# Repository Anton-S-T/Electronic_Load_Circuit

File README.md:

#Electronic_Load_Circuit

A circuit to sink 3A at a Voltage of up to 30V

Layout:

WIP

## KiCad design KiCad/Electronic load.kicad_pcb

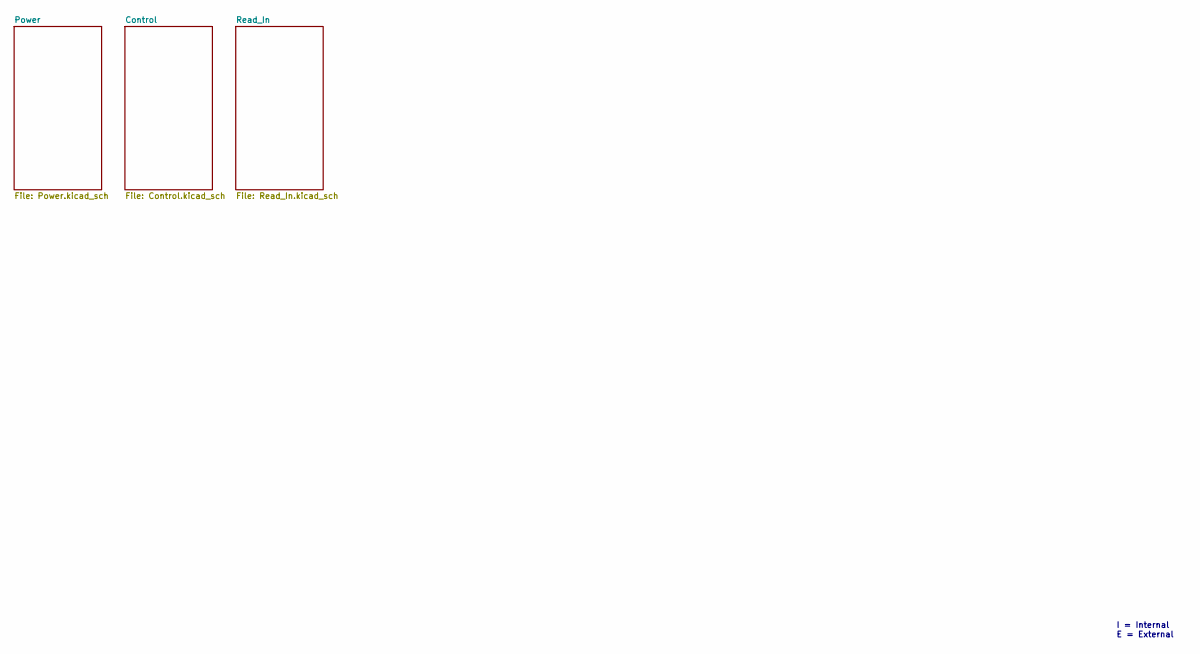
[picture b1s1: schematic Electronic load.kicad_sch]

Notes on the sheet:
I = Internal E = External

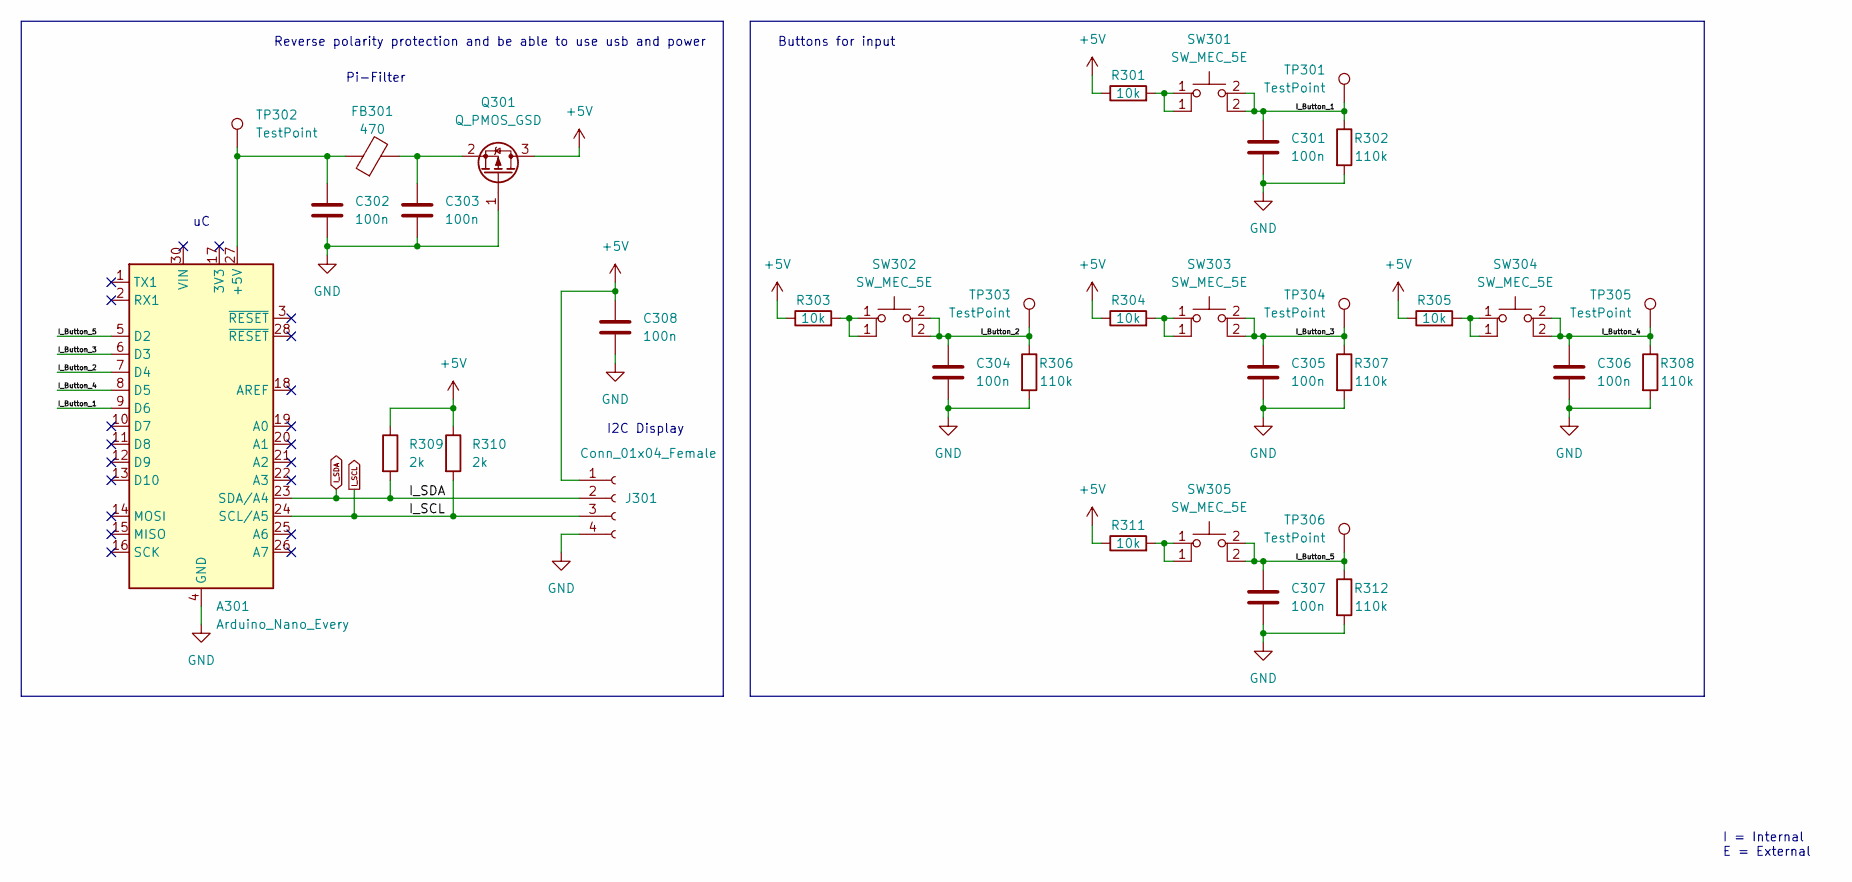
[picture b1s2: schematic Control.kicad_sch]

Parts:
A301: Arduino_Nano_Every; Arduino_Nano
C301, C302, C303, C304, C305, C306, C307, C308: 100n; C_0603_1608Metric
FB301: 470; R_0603_1608Metric
J301: Conn_01x04_Female; TerminalBlock_bornier-4_P5.08mm
Q301: Q_PMOS_GSD; SOT-23
R301, R303, R304, R305, R311: 10k; R_0603_1608Metric
R302, R306, R307, R308, R312: 110k; R_0603_1608Metric
R309, R310: 2k; R_0805_2012Metric
SW301, SW302, SW303, SW304, SW305: SW_MEC_5E; SW_PUSH_6mm
TP301, TP302, TP303, TP304, TP305, TP306: TestPoint; TestPoint_Pad_D1.0mm

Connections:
+5V: C308.1, J301.1, Q301.3 (D), R301.1, R303.1, R304.1, R305.1, R309.1, R310.1, R311.1; also elsewhere on the board
/Control/I_Button_1: A301.9 (D6), C301.1, R302.1, SW301.2 (K), TP301.1
/Control/I_Button_2: A301.7 (D4), C304.1, R306.1, SW302.2 (K), TP303.1
/Control/I_Button_3: A301.6 (D3), C305.1, R307.1, SW303.2 (K), TP304.1
/Control/I_Button_4: A301.8 (D5), C306.1, R308.1, SW304.2 (K), TP305.1
/Control/I_Button_5: A301.5 (D2), C307.1, R312.1, SW305.2 (K), TP306.1
GND: A301.4 (GND), A301.29 (GND), C301.2, C302.2, C303.2, C304.2, C305.2, C306.2, C307.2, C308.2, J301.4, Q301.1 (G), R302.2, R306.2, R307.2, R308.2, R312.2; also elsewhere on the board
I_SCL: A301.24 (SCL/A5), J301.3, R310.2; also elsewhere on the board
I_SDA: A301.23 (SDA/A4), J301.2, R309.2; also elsewhere on the board
unnamed: A301.27 (+5V), C302.1, FB301.1, TP302.1
unnamed: C303.1, FB301.2, Q301.2 (S)
unnamed: R301.2, SW301.1
unnamed: R303.2, SW302.1
unnamed: R304.2, SW303.1
unnamed: R305.2, SW304.1
unnamed: R311.2, SW305.1

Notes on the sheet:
Pi-Filter
I = Internal E = External
Buttons for input
I2C Display
Reverse polarity protection and be able to use usb and power

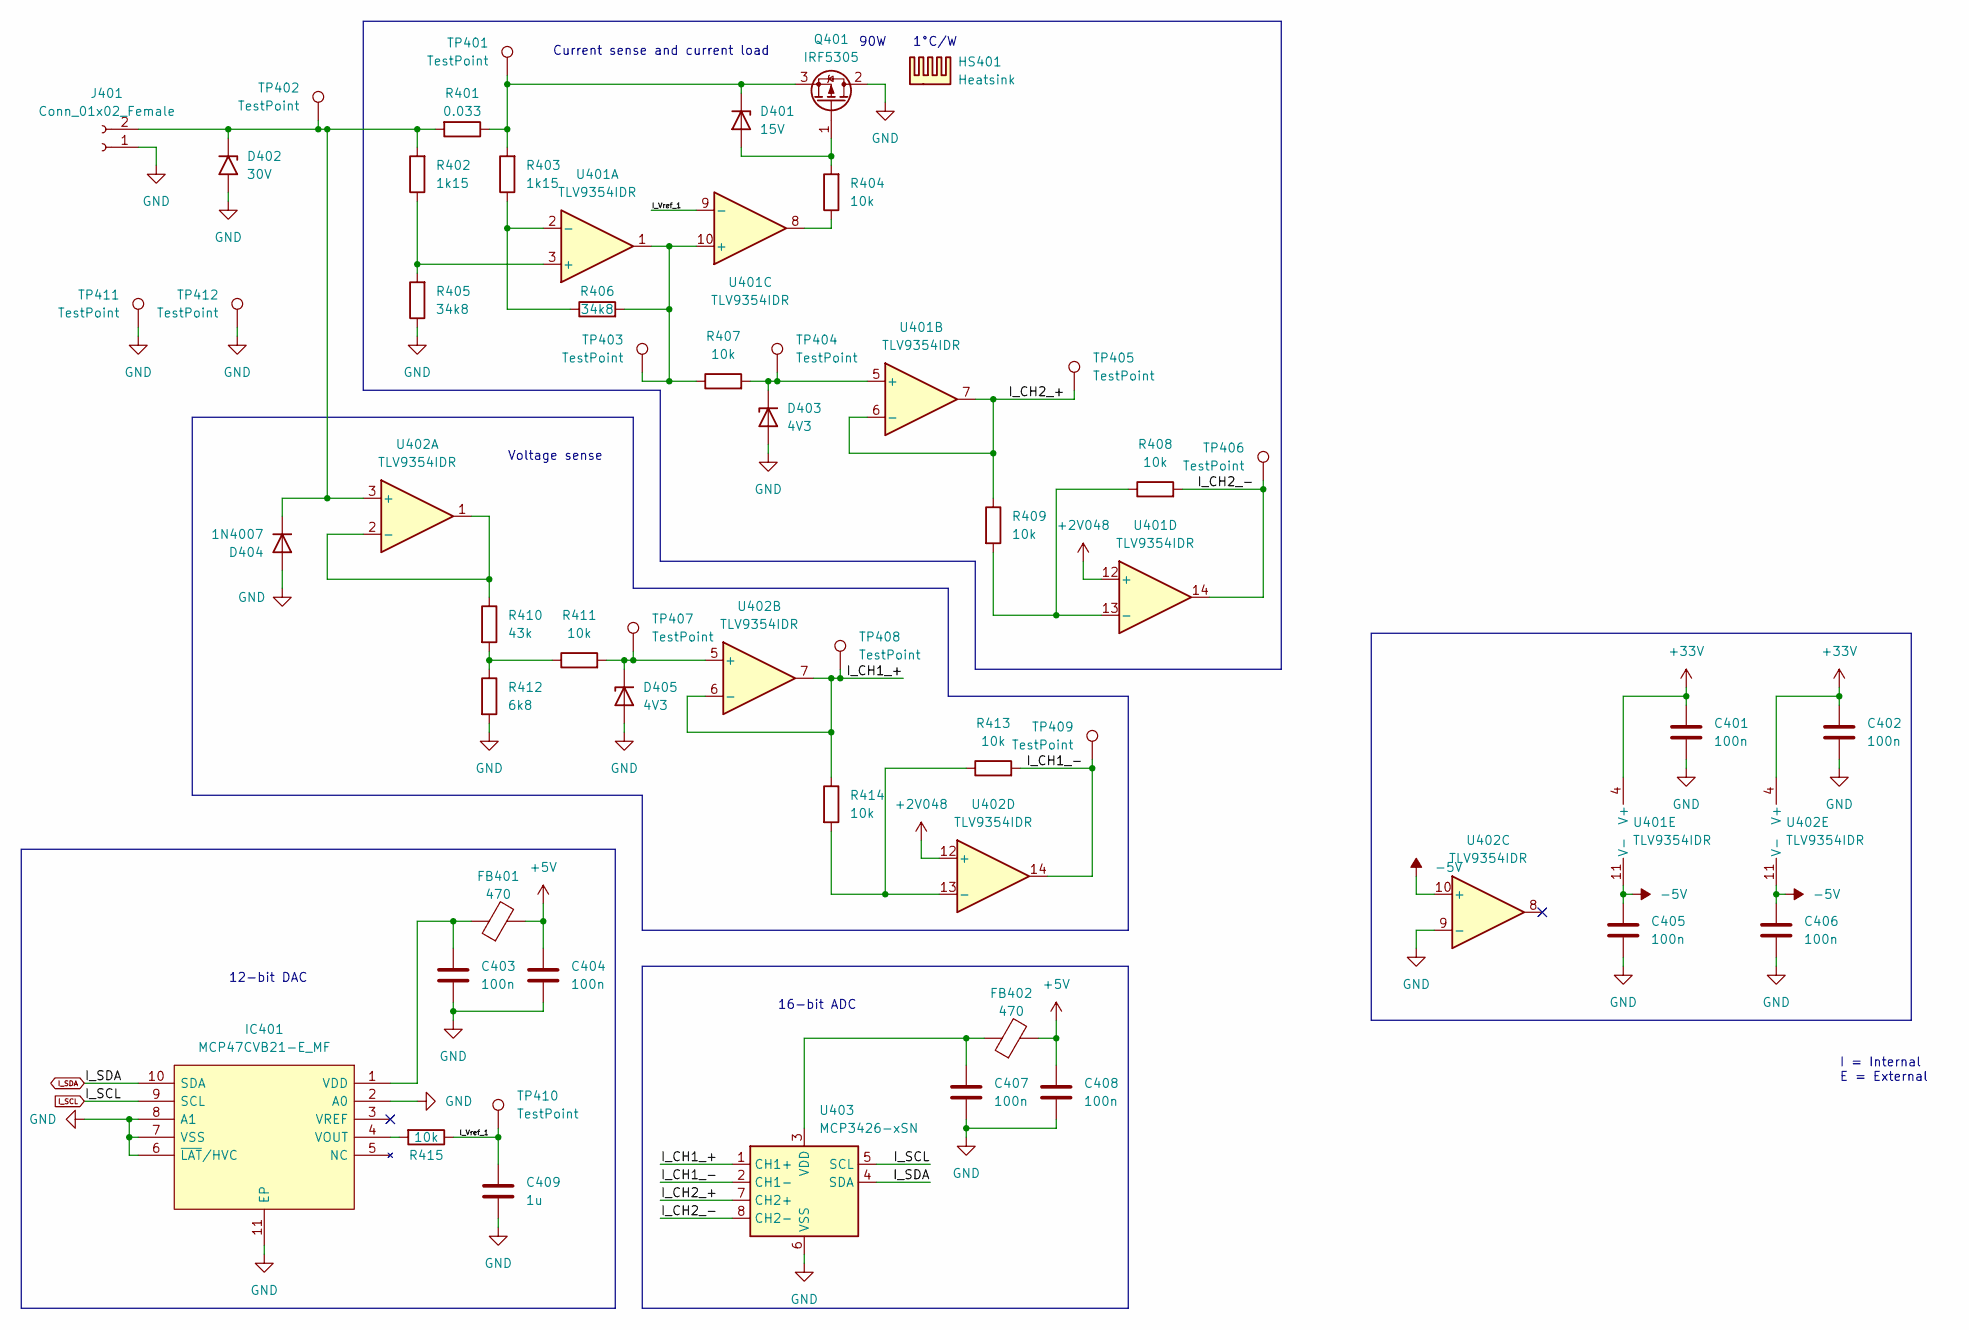
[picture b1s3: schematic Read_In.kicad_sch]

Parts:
C401, C402, C403, C404, C405, C406, C407, C408: 100n; C_0603_1608Metric
C409: 1u; C_0603_1608Metric
D401: 15V; D_SOD-123
D402: 30V; D_SMB
D403, D405: 4V3; D_SOD-123
D404: 1N4007; D_DO-41_SOD81_P10.16mm_Horizontal
FB401, FB402: 470; R_0603_1608Metric
HS401: Heatsink
IC401: MCP47CVB21-E_MF; DFN-10-1EP_3x3mm_P0.5mm_EP1.65x2.38mm_ThermalVias; Mouser Part Number 579-MCP47CVB21-E/MF
J401: Conn_01x02_Female; TerminalBlock_bornier-2_P5.08mm
Q401: IRF5305; TO-220-3_Vertical
R401: 0.033; R_1206_3216Metric
R402, R403: 1k15; R_0805_2012Metric
R404, R407, R408, R409, R411, R413, R414, R415: 10k; R_0603_1608Metric
R405, R406: 34k8; R_0603_1608Metric
R410: 43k; R_0603_1608Metric
R412: 6k8; R_0603_1608Metric
TP401, TP402, TP403, TP404, TP405, TP406, TP407, TP408, TP409, TP410, TP411, TP412: TestPoint; TestPoint_Pad_D1.0mm
U401, U402: TLV9354IDR; SOIC-14_3.9x8.7mm_P1.27mm
U403: MCP3426-xSN; SOIC-8-1EP_3.9x4.9mm_P1.27mm_EP2.29x3mm

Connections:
+2V048: U401.12 (+), U402.12 (+); also elsewhere on the board
+5V: C404.1, C408.1, FB401.2, FB402.2; also elsewhere on the board
-5V: C405.1, C406.1, U401.11 (V-), U402.10 (+), U402.11 (V-); also elsewhere on the board
/Read_In/I_CH1_+: R414.1, TP408.1, U402.6 (-), U402.7, U403.1 (CH1+)
/Read_In/I_CH1_-: R413.2, TP409.1, U402.14, U403.2 (CH1-)
/Read_In/I_CH2_+: R409.1, TP405.1, U401.6 (-), U401.7, U403.7 (CH2+)
/Read_In/I_CH2_-: R408.2, TP406.1, U401.14, U403.8 (CH2-)
/Read_In/I_Vref_1: C409.1, R415.1, TP410.1, U401.9 (-)
GND: C401.2, C402.2, C403.2, C404.2, C405.2, C406.2, C407.2, C408.2, C409.2, D402.2 (A2), D403.2 (A), D404.2 (A), D405.2 (A), IC401.2 (A0), IC401.6 (~LAT/HVC), IC401.7 (VSS), IC401.8 (A1), IC401.11 (EP), J401.1, Q401.2 (D), R405.1, R412.2, TP411.1, TP412.1, U402.9 (-), U403.6 (VSS); also elsewhere on the board
I_SCL: IC401.9 (SCL), U403.5 (SCL); also elsewhere on the board
I_SDA: IC401.10 (SDA), U403.4 (SDA); also elsewhere on the board
unnamed: C403.1, FB401.1, IC401.1 (VDD)
unnamed: C407.1, FB402.1, U403.3 (VDD)
unnamed: D401.1 (K), Q401.3 (S), R401.1, R403.2, TP401.1
unnamed: D401.2 (A), Q401.1 (G), R404.2
unnamed: D402.1 (A1), D404.1 (K), J401.2, R401.2, R402.2, TP402.1, U402.3 (+)
unnamed: D403.1 (K), R407.2, TP404.1, U401.5 (+)
unnamed: D405.1 (K), R411.2, TP407.1, U402.5 (+)
unnamed: IC401.4 (VOUT), R415.2
unnamed: R402.1, R405.2, U401.3 (+)
unnamed: R403.1, R406.1, U401.2 (-)
unnamed: R404.1, U401.8
unnamed: R406.2, R407.1, TP403.1, U401.1, U401.10 (+)
unnamed: R408.1, R409.2, U401.13 (-)
unnamed: R410.1, U402.1, U402.2 (-)
unnamed: R410.2, R411.1, R412.1
unnamed: R413.1, R414.2, U402.13 (-)

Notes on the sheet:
Current sense and current load
I = Internal E = External
Voltage sense
90W
1°C/W
16-bit ADC
12-bit DAC

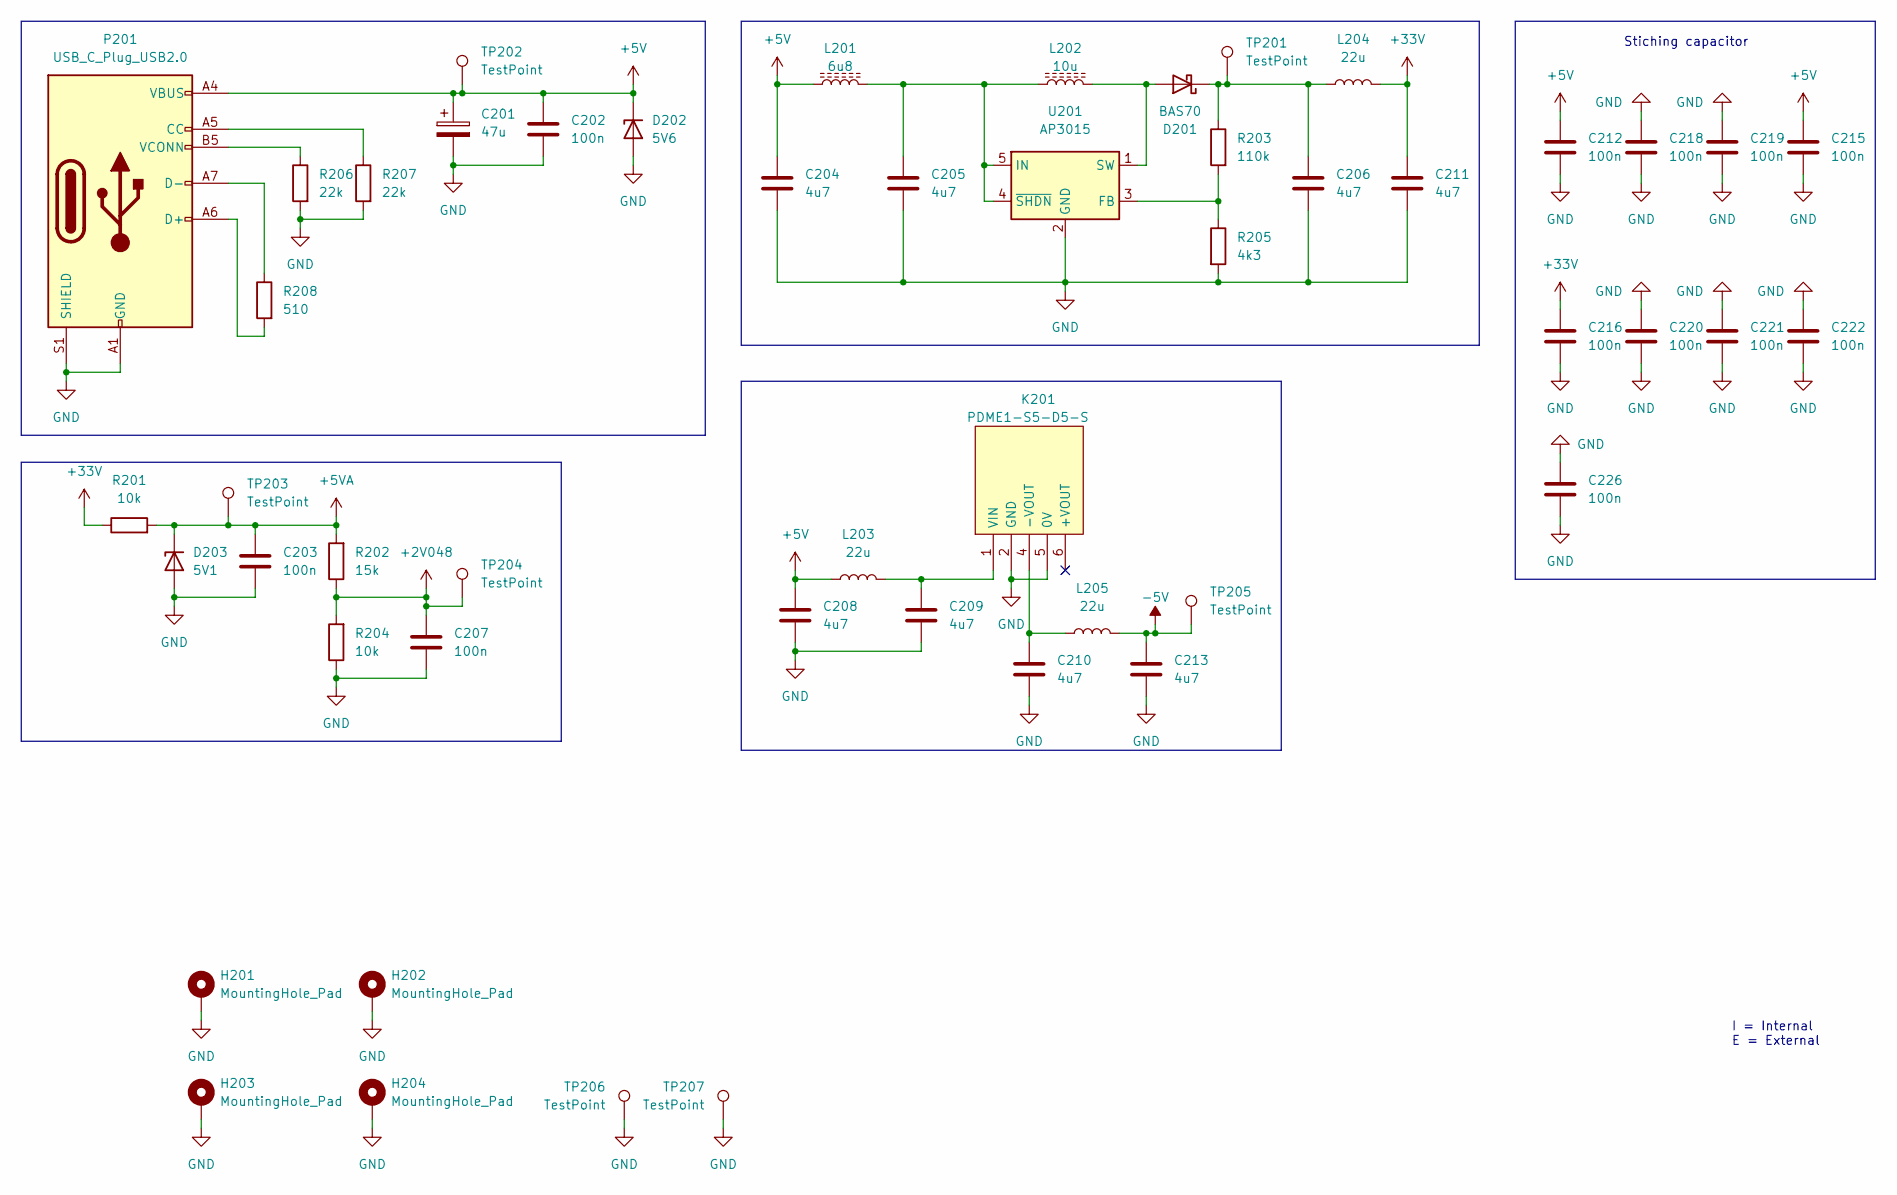
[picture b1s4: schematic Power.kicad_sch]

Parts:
C201: 47u; CP_Elec_8x6.9
C202, C203, C207, C212, C215, C216, C218, C219, C220, C221, C222, C226: 100n; C_0603_1608Metric
C204, C205, C206, C208, C209, C210, C211, C213: 4u7; C_0805_2012Metric
D201: BAS70; D_SOD-323
D202: 5V6; D_SOD-123
D203: 5V1; D_SOD-123
H201, H202, H203, H204: MountingHole_Pad; MountingHole_3.2mm_M3_Pad_TopBottom
K201: PDME1-S5-D5-S; PDME1S5D5S; Mouser Part Number 490-PDME1-S5-D5-S
L201: 6u8; L_Bourns-SRN4018
L202: 10u; L_Bourns_SRN6045TA
L203, L204, L205: 22u; L_0603_1608Metric
P201: USB_C_Plug_USB2.0; USB_C_Receptacle_HRO_TYPE-C-31-M-12
R201, R204: 10k; R_0603_1608Metric
R202: 15k; R_0603_1608Metric
R203: 110k; R_0603_1608Metric
R205: 4k3; R_0603_1608Metric
R206, R207: 22k; R_0603_1608Metric
R208: 510; R_0805_2012Metric
TP201, TP202, TP203, TP204, TP205, TP206, TP207: TestPoint; TestPoint_Pad_D1.0mm
U201: AP3015; SOT-23-5

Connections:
+2V048: C207.1, R202.1, R204.2, TP204.1; also elsewhere on the board
+5V: C201.1, C202.1, C204.1, C208.1, C212.1, C215.1, D202.1 (K), L201.1, L203.1, P201.A4 (VBUS), P201.A9 (VBUS), P201.B4 (VBUS), P201.B9 (VBUS), TP202.1; also elsewhere on the board
+5VA: C203.1, D203.1 (K), R201.2, R202.2, TP203.1
-5V: C213.1, L205.2, TP205.1; also elsewhere on the board
GND: C201.2, C202.2, C203.2, C204.2, C205.2, C206.2, C207.2, C208.2, C209.2, C210.2, C211.2, C212.2, C213.2, C215.2, C216.2, C218.1, C218.2, C219.1, C219.2, C220.1, C220.2, C221.1, C221.2, C222.1, C222.2, C226.1, C226.2, D202.2 (A), D203.2 (A), H201.1, H202.1, H203.1, H204.1, K201.2 (GND), K201.5 (0V), P201.A1 (GND), P201.A12 (GND), P201.B1 (GND), P201.B12 (GND), P201.S1 (SHIELD), R204.1, R205.2, R206.2, R207.2, TP206.1, TP207.1, U201.2 (GND); also elsewhere on the board
unnamed: C205.1, L201.2, L202.1, U201.4 (~SHDN), U201.5 (IN)
unnamed: C206.1, D201.1 (K), L204.1, R203.1, TP201.1
unnamed: C209.1, K201.1 (VIN), L203.2
unnamed: C210.1, K201.4 (-VOUT), L205.1
unnamed: D201.2 (A), L202.2, U201.1 (SW)
unnamed: P201.A5 (CC), R207.1
unnamed: P201.A6 (D+), R208.2
unnamed: P201.A7 (D-), R208.1
unnamed: P201.B5 (VCONN), R206.1
unnamed: R203.2, R205.1, U201.3 (FB)

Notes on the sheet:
I = Internal E = External
Stiching capacitor

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
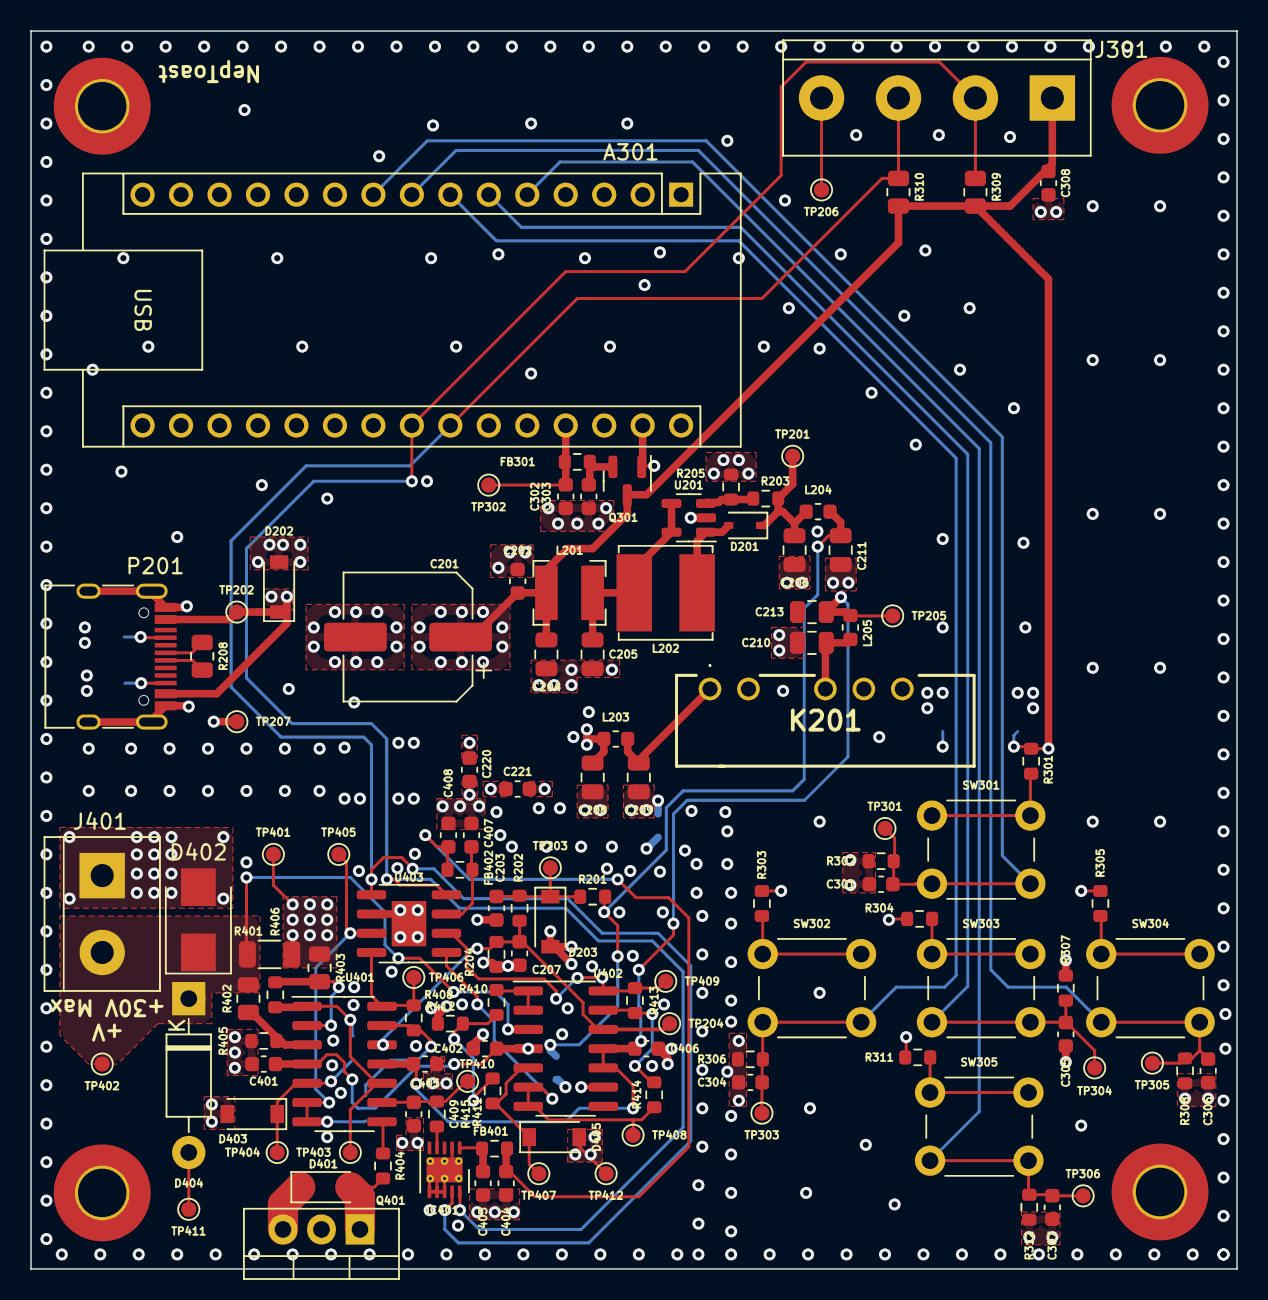
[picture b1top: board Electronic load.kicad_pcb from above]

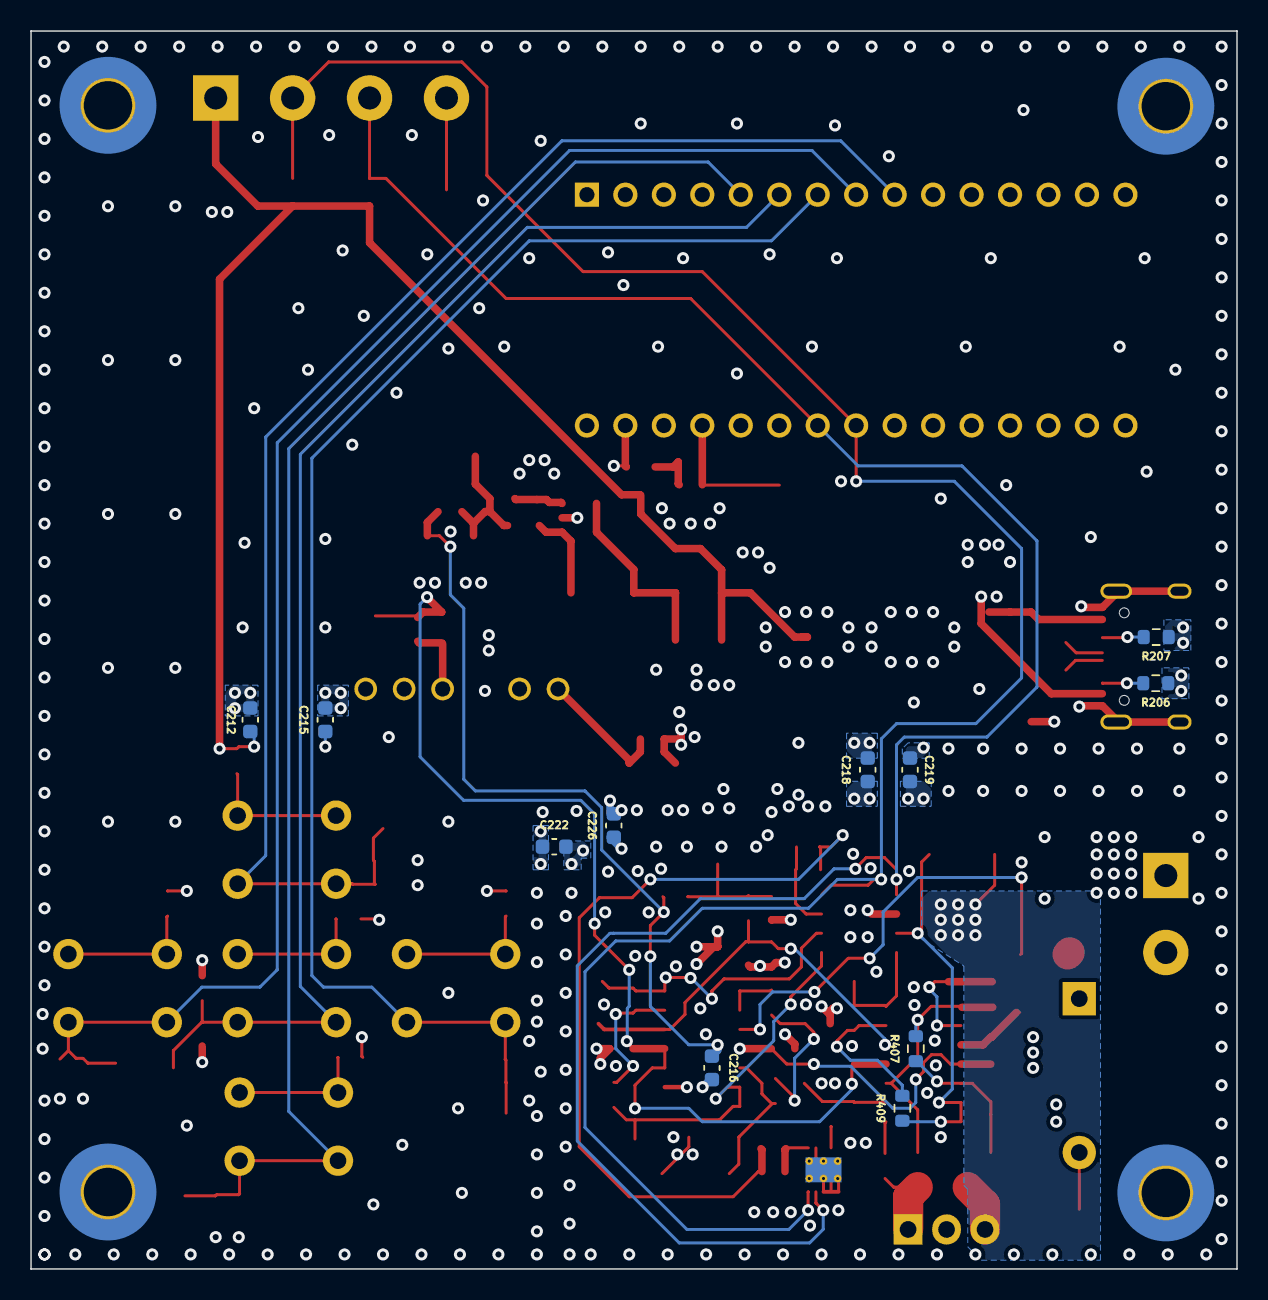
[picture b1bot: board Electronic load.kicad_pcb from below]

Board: 4 copper layers, 79.6 x 81.7 mm, 135 parts (11 on the bottom side), 51 nets.
